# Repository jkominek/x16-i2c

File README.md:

Rough draft of an I2C expansion card for the [Commander X16](https://www.commanderx16.com/)

I don't have any real hardware, and haven't fabbed this. So there's little reason to believe it works.

* Features
  * PCA9548A I2C eight port multiplexer, so you can use a lot of I2C devices without loading the bus down. Also lets you use multiple identical devices, which would otherwise have conflicting addresses.
  * Four I2C ports are brought out [SparkFun Qwiic](https://www.sparkfun.com/qwiic)-style, with 3.3V power.
    * Why that connector? Sparkfun has a lot of Qwiic hardware, and Adafruit as a bunch of [STEMMA QT](https://www.adafruit.com/category/1018) hardware, which is compatible. Some other companies have some similar products. This gets you dozens of compatible IO devices in one fell swoop.
  * Three are headers on the board, with 5V power, for use "inside the case"
  * Last port is on a PCA9615 differential I2C transceiver, for very distant I2C devices.
    * It provides 3.3V and 12V.
    * Intended to be compatible with the [Sparkfun QwiicBus Endpoint](https://www.sparkfun.com/products/16988)
  * One mandatory 3.3V regulator for the external I2C ports.
  * You can add one or two other additional regulators, to provide more power to your I2C devices.

I'll revisit and revise this as more docs come out, and whenever I get real hardware.

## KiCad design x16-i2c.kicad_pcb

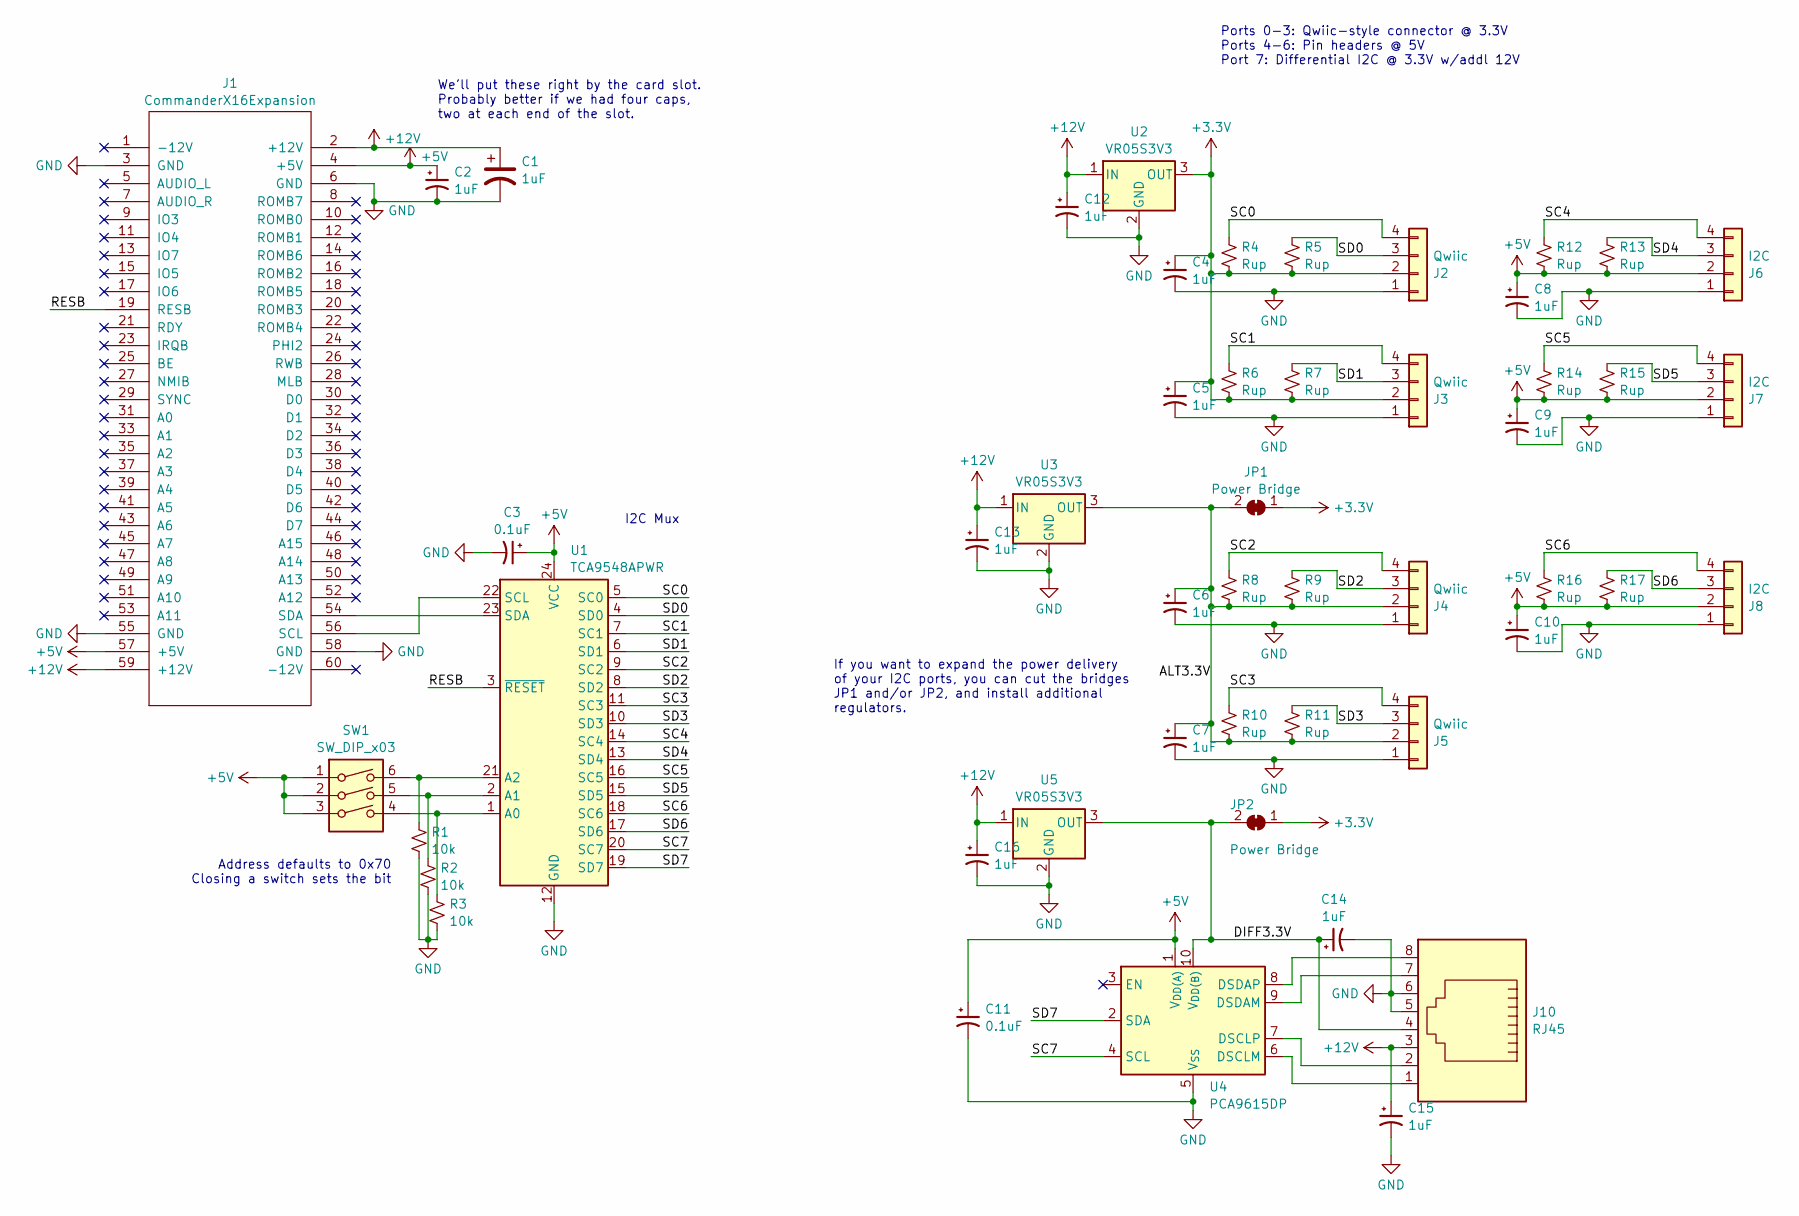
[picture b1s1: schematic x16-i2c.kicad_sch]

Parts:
C1, C2, C4, C5, C6, C7, C8, C9, C10, C12, C13, C14, C15, C16: 1uF; C_0805_2012Metric
C3, C11: 0.1uF; C_0805_2012Metric
J1: CommanderX16Expansion
J2, J3, J4, J5: Qwiic; JST_SH_SM04B-SRSS-TB_1x04-1MP_P1.00mm_Horizontal
J6, J7, J8: I2C; PinHeader_1x04_P2.54mm_Vertical
J10: RJ45; RJ45_8
JP1, JP2: Power Bridge; SolderJumper-2_P1.3mm_Bridged_RoundedPad1.0x1.5mm
R1, R2, R3: 10k; R_0805_2012Metric
R4, R5, R6, R7, R8, R9, R10, R11, R12, R13, R14, R15, R16, R17: Rup; R_0805_2012Metric
SW1: SW_DIP_x03; DIP-6_W7.62mm
U1: TCA9548APWR; TSSOP-24_4.4x7.8mm_P0.65mm
U2, U3, U5: VR05S3V3; TO-220-3_Vertical
U4: PCA9615DP; TSSOP-10_3x3mm_P0.5mm

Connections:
+3.3V: C4.1, C5.1, J2.2, J3.2, JP1.1 (A), JP2.1 (A), R4.2, R5.2, R6.2, R7.2, U2.3 (OUT)
+5V: C2.1, C3.1, C8.1, C9.1, C10.1, C11.1, J1.4 (+5V), J1.57 (+5V), J6.2, J7.2, J8.2, R12.2, R13.2, R14.2, R15.2, R16.2, R17.2, SW1.1, SW1.2, SW1.3, U1.24 (VCC), U4.1 (V_{DD(A)})
+12V: C1.1, C12.1, C13.1, C15.1, C16.1, J1.2 (+12V), J1.59 (+12V), J10.3, U2.1 (IN), U3.1 (IN), U5.1 (IN)
/ALT3.3V: C6.1, C7.1, J4.2, J5.2, JP1.2 (B), R8.2, R9.2, R10.2, R11.2, U3.3 (OUT)
/DIFF3.3V: C14.1, J10.4, JP2.2 (B), U4.10 (V_{DD(B)}), U5.3 (OUT)
/RESB: J1.19 (RESB), U1.3 (~RESET)
/SC0: J2.4, R4.1, U1.5 (SC0)
/SC1: J3.4, R6.1, U1.7 (SC1)
/SC2: J4.4, R8.1, U1.9 (SC2)
/SC3: J5.4, R10.1, U1.11 (SC3)
/SC4: J6.4, R12.1, U1.14 (SC4)
/SC5: J7.4, R14.1, U1.16 (SC5)
/SC6: J8.4, R16.1, U1.18 (SC6)
/SC7: U1.20 (SC7), U4.4 (SCL)
/SD0: J2.3, R5.1, U1.4 (SD0)
/SD1: J3.3, R7.1, U1.6 (SD1)
/SD2: J4.3, R9.1, U1.8 (SD2)
/SD3: J5.3, R11.1, U1.10 (SD3)
/SD4: J6.3, R13.1, U1.13 (SD4)
/SD5: J7.3, R15.1, U1.15 (SD5)
/SD6: J8.3, R17.1, U1.17 (SD6)
/SD7: U1.19 (SD7), U4.2 (SDA)
GND: C1.2, C2.2, C3.2, C4.2, C5.2, C6.2, C7.2, C8.2, C9.2, C10.2, C11.2, C12.2, C13.2, C14.2, C15.2, C16.2, J1.3 (GND), J1.6 (GND), J1.55 (GND), J1.58 (GND), J2.1, J3.1, J4.1, J5.1, J6.1, J7.1, J8.1, J10.5, J10.6, R1.1, R2.1, R3.1, U1.12 (GND), U2.2 (GND), U3.2 (GND), U4.5 (V_{SS}), U5.2 (GND)
unnamed: J1.56 (SCL), U1.22 (SCL)
unnamed: J1.54 (SDA), U1.23 (SDA)
unnamed: R3.2, SW1.4, U1.1 (A0)
unnamed: R2.2, SW1.5, U1.2 (A1)
unnamed: R1.2, SW1.6, U1.21 (A2)
unnamed: J10.1, U4.6 (DSCLM)
unnamed: J10.2, U4.7 (DSCLP)
unnamed: J10.7, U4.9 (DSDAM)
unnamed: J10.8, U4.8 (DSDAP)

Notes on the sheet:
We'll put these right by the card slot. Probably better if we had four caps, two at each end of the slot.
Ports 0-3: Qwiic-style connector @ 3.3V Ports 4-6: Pin headers @ 5V Port 7: Differential I2C @ 3.3V w/addl 12V
If you want to expand the power delivery of your I2C ports, you can cut the bridges JP1 and/or JP2, and install additional regulators.
I2C Mux
Address defaults to 0x70 Closing a switch sets the bit

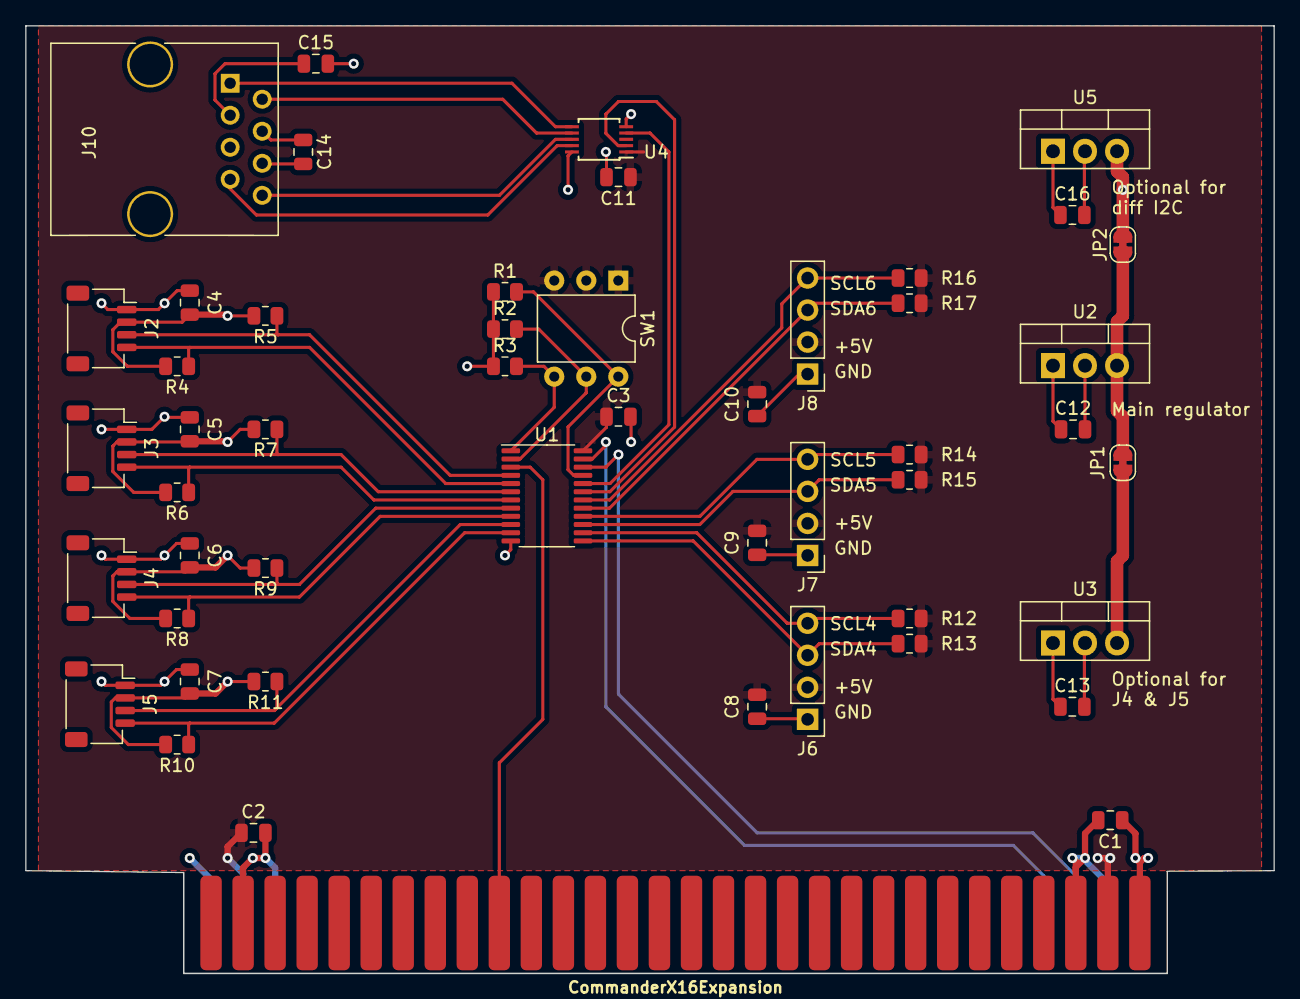
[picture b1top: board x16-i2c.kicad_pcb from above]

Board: 4 copper layers, 99.0 x 75.1 mm, 50 parts (0 on the bottom side), 32 nets.

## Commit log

2023-10-31 initial version
2023-10-31 added a license
2023-11-01 expanded on design motivation in the README
